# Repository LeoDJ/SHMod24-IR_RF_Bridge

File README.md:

# SHMod24 Addon: RF/IR Bridge

This addon is meant to be plugged onto a [SHMod24](https://github.com/LeoDJ/SHMod24) base board.
It provides the ability to send and receive infrared and 433MHz RF remote control codes.

**Current status**: a prototype PCB batch has been ordered and will be tested for functionality

## 3D Preview

|  |  |
| :--------------- | :------------------ |
|              |                 |

## BOM
There are multiple different module groups that can be populated.

 In the table is listed, which components to populate for a given module:

| Module                         | Reference | Part                    |
| :----------------------------- | :-------- | :---------------------- |
| **IR LED Array**               | Q1        | AO3400A                 |
|                                | R1        | 15Ω                     |
|                                | R2        | 10k                     |
|                                | R3, R4    | 2Ω                      |
|                                | C1        | 22µF, 1210              |
|                                | D1 - D7   | IR LED 5mm              |
|                                |           |                         |
| **IR Receiver Array**          | R7        | 100Ω                    |
|                                | C4        | 100µF, 6.3x5.8          |
|                                | R8        | 47k                     |
|                                | C6 - C9   | 100n                    |
|                                | IR1 - IR4 | VS1838b                 |
|                                |           |                         |
| **433MHz 12V Boost Converter** | U1        | MT3608                  |
| Can also be bypassed by        | R5        | 180k                    |
| bridging L1 and D8 to run      | R6        | 10k                     |
| 433MHz transmitter at 3.3V     | D8        | SS34 Schottky, SMA      |
|                                | C2, C3    | 22µF, 1210              |
|                                | L1        | 4.7µH, 0630             |
|                                |           |                         |
| **433MHz Receiver**            | RF1       | Generic China 433MHz RX |
|                                |           |                         |
| **433MHz Transmitter**         | RF2       | Generic China 433MHz TX |

## Project installation
- Make sure to run `git clone` with `--recurse-submodules` to include the necessary libraries too.

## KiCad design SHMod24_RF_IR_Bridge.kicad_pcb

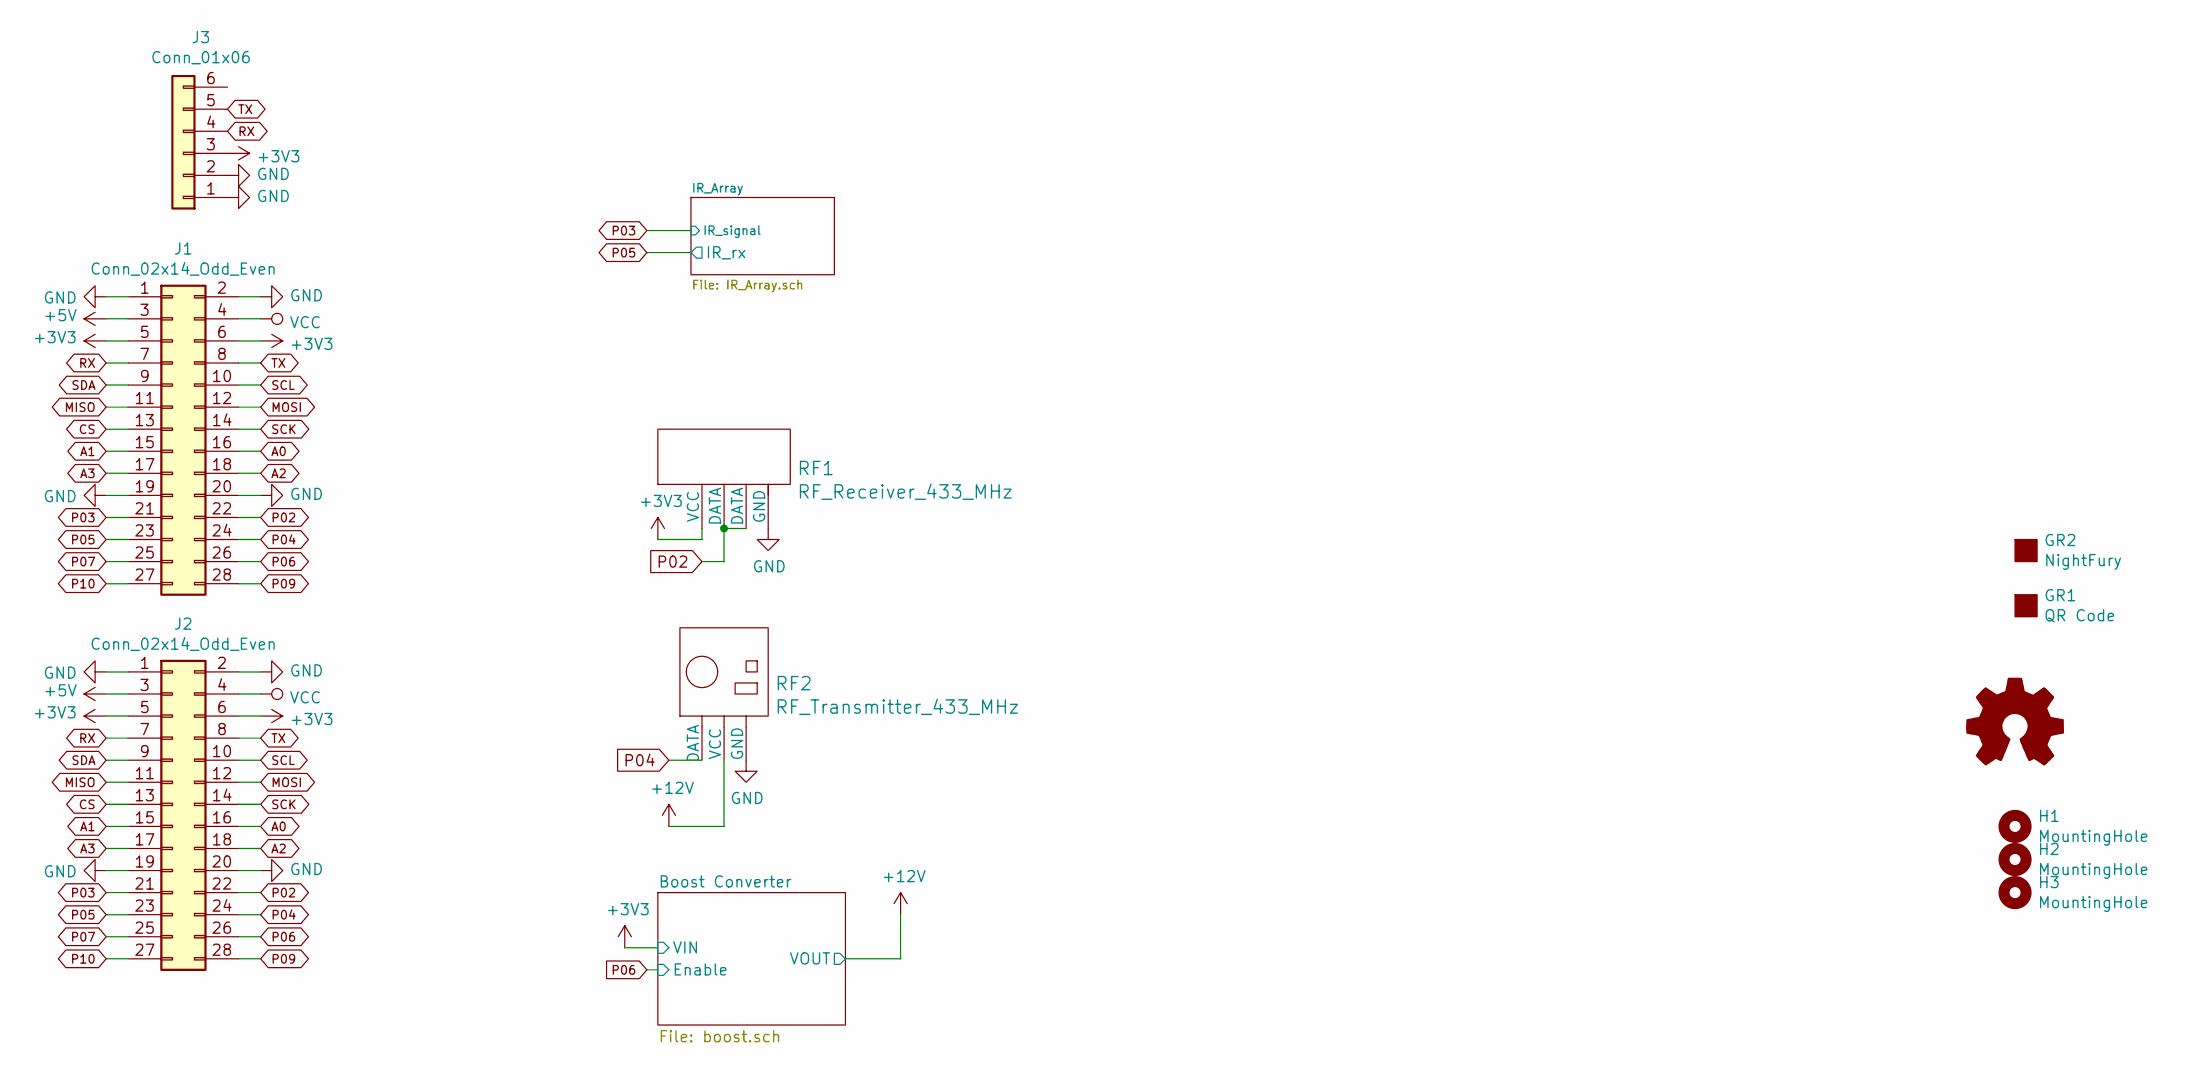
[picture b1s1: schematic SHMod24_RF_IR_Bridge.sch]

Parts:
GR1: QR Code; QR_Code_SHMod24-IRRF
GR2: NightFury; NightFury_Roll_8.0x6.1
H1, H2, H3: MountingHole; MountingHole_3.2mm_M3
J1: Conn_02x14_Odd_Even; PinSocket_2x14_P2.54mm_Vertical
J2: Conn_02x14_Odd_Even; PinSocket_2x14_P2.54mm_Vertical_SMD
J3: Conn_01x06; PinHeader_1x06_P2.54mm_Vertical
LOGO1: Logo_Open_Hardware_Small; OSHW-Logo2_7.3x6mm_SilkScreen
RF1: RF_Receiver_433_MHz
RF2: RF_Transmitter_433_MHz

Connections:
+3V3: J1.5, J1.6, J2.5, J2.6, J3.3, RF1.1 (VCC); also elsewhere on the board
+5V: J1.3, J2.3
+12V: RF2.2 (VCC); also elsewhere on the board
A0: J1.16, J2.16
A1: J1.15, J2.15
A2: J1.18, J2.18
A3: J1.17, J2.17
CS: J1.13, J2.13
GND: J1.1, J1.2, J1.19, J1.20, J2.1, J2.2, J2.19, J2.20, J3.1, J3.2, RF1.4 (GND), RF2.3 (GND); also elsewhere on the board
MISO: J1.11, J2.11
MOSI: J1.12, J2.12
P02: J1.22, J2.22, RF1.2 (DATA), RF1.3 (DATA)
P03: J1.21, J2.21; also elsewhere on the board
P04: J1.24, J2.24, RF2.1 (DATA)
P05: J1.23, J2.23; also elsewhere on the board
P06: J1.26, J2.26; also elsewhere on the board
P07: J1.25, J2.25
P09: J1.28, J2.28
P10: J1.27, J2.27
RX: J1.7, J2.7, J3.4
SCK: J1.14, J2.14
SCL: J1.10, J2.10
SDA: J1.9, J2.9
TX: J1.8, J2.8, J3.5
VCC: J1.4, J2.4

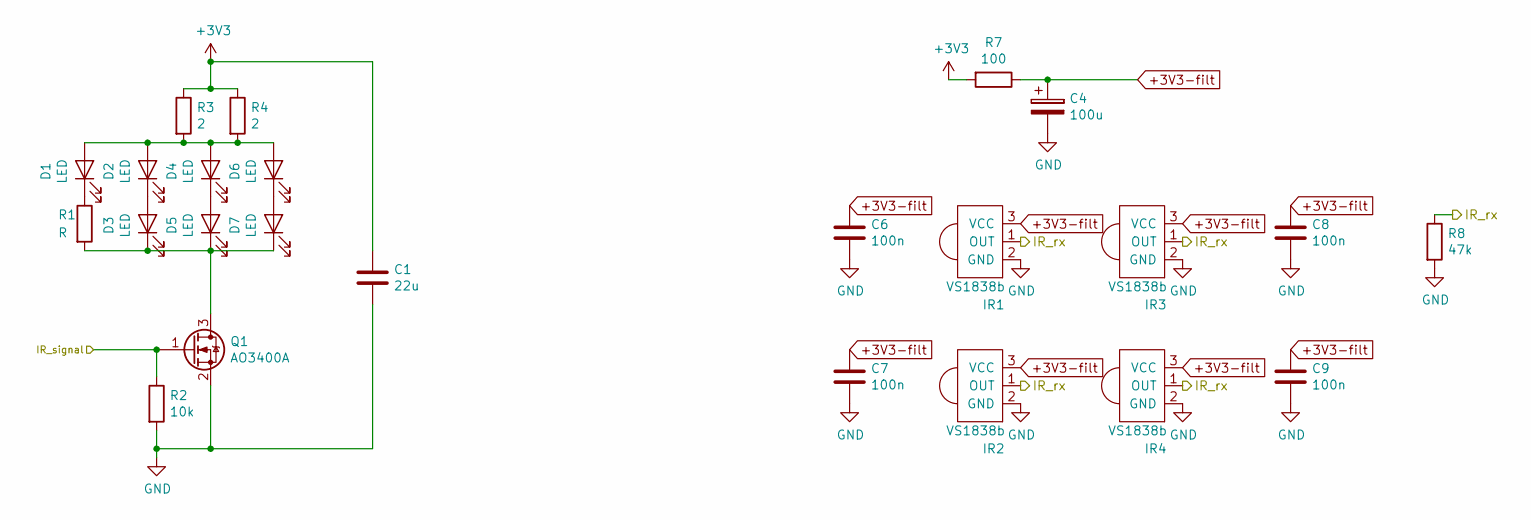
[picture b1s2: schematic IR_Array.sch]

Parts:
C1: 22u; C_1210_3225Metric
C4: 100u; CP_Elec_6.3x5.8
C6, C7, C8, C9: 100n; C_0805_2012Metric
D1: LED; LED_D5.0mm_IRBlack
D2, D3, D4, D5, D6, D7: LED; LED_D5.0mm_Horizontal_O1.27mm_Z9.0mm
IR1, IR2, IR3, IR4: VS1838b
Q1: AO3400A; SOT-23
R1: R; R_0805_2012Metric
R2: 10k; R_0805_2012Metric
R3, R4: 2; R_0805_2012Metric
R7: 100; R_0805_2012Metric
R8: 47k; R_0805_2012Metric

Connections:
+3V3: C1.1, R3.1, R4.1, R7.2; also elsewhere on the board
+3V3-filt: C4.1, C6.1, C7.1, C8.1, C9.1, IR1.3 (VCC), IR2.3 (VCC), IR3.3 (VCC), IR4.3 (VCC), R7.1
GND: C1.2, C4.2, C6.2, C7.2, C8.2, C9.2, IR1.2 (GND), IR2.2 (GND), IR3.2 (GND), IR4.2 (GND), Q1.2 (S), R2.2, R8.2; also elsewhere on the board
unnamed: D1.1 (K), R1.1
unnamed: D1.2 (A), D2.2 (A), D4.2 (A), D6.2 (A), R3.2, R4.2
unnamed: D2.1 (K), D3.2 (A)
unnamed: D3.1 (K), D5.1 (K), D7.1 (K), Q1.3 (D), R1.2
unnamed: D4.1 (K), D5.2 (A)
unnamed: D6.1 (K), D7.2 (A)
P03: Q1.1 (G), R2.1; also elsewhere on the board
P05: IR1.1 (OUT), IR2.1 (OUT), IR3.1 (OUT), IR4.1 (OUT), R8.1; also elsewhere on the board

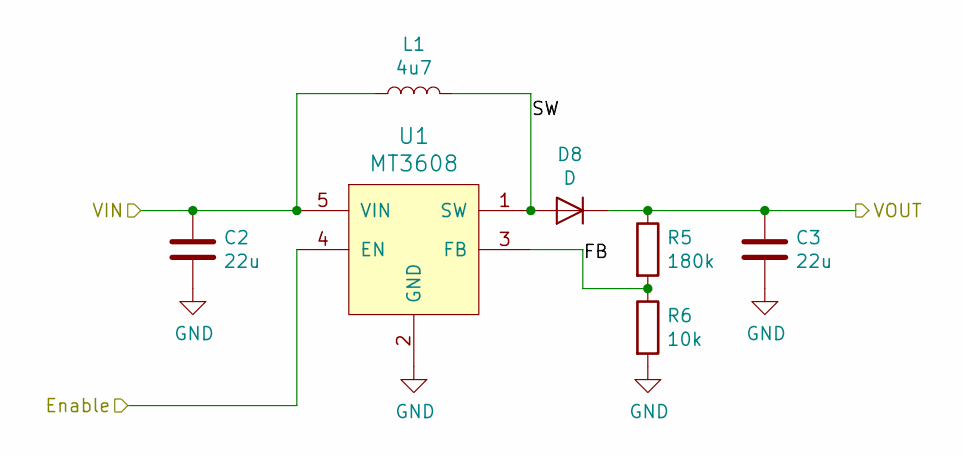
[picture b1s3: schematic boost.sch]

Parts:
C2, C3: 22u; C_1210_3225Metric
D8: D; D_SMA
L1: 4u7; L_0630
R5: 180k; R_0805_2012Metric
R6: 10k; R_0805_2012Metric
U1: MT3608; SOT-23-6

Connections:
+3V3: C2.1, L1.1, U1.5 (VIN); also elsewhere on the board
+12V: C3.1, D8.1 (K), R5.1; also elsewhere on the board
/Boost Converter/FB: R5.2, R6.1, U1.3 (FB)
/Boost Converter/SW: D8.2 (A), L1.2, U1.1 (SW)
GND: C2.2, C3.2, R6.2, U1.2 (GND); also elsewhere on the board
P06: U1.4 (EN); also elsewhere on the board

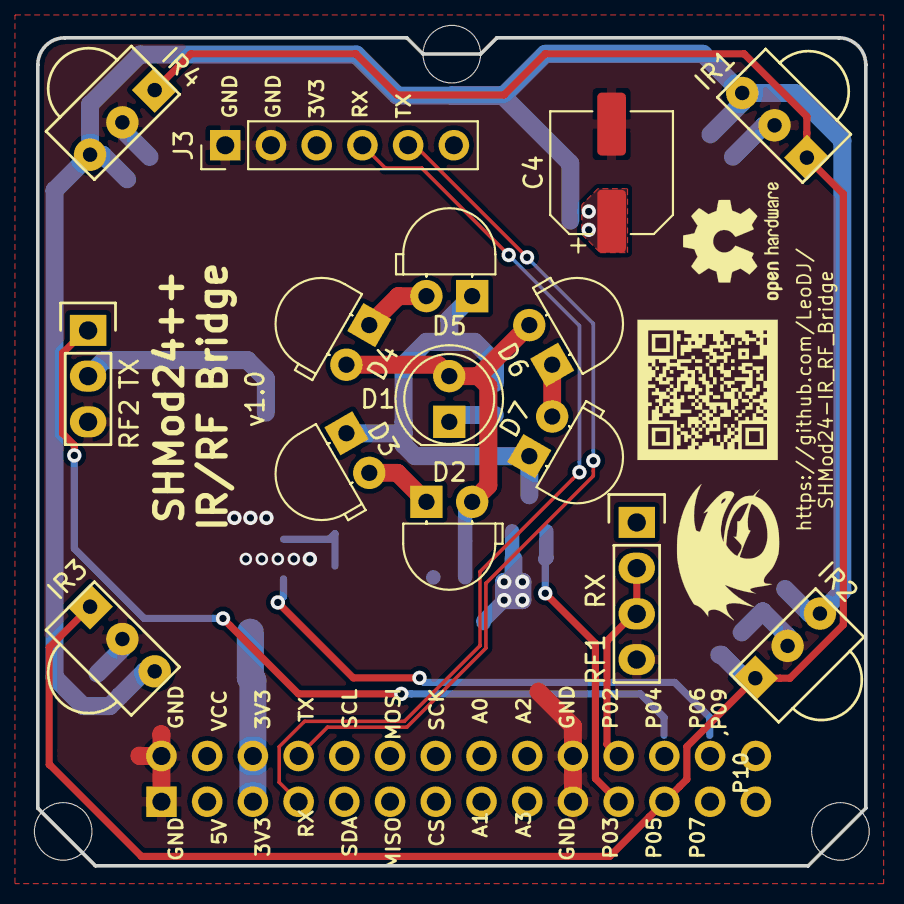
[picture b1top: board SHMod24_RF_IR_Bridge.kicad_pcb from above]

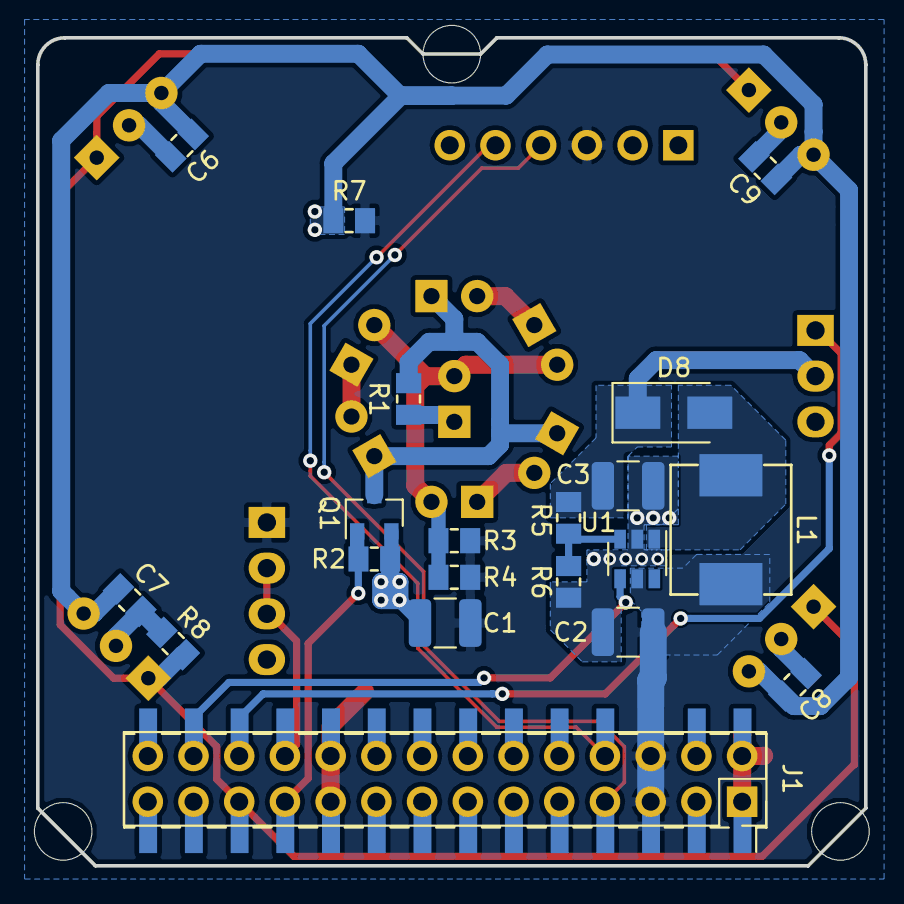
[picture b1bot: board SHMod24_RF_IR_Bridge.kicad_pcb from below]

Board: 2 copper layers, 46.0 x 46.0 mm, 42 parts (21 on the bottom side), 34 nets.

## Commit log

2019-01-15 initial commit
    basic SHMod24 addon board layout with holes and header done
2019-01-16 add smd pin header option
2019-01-17 design IR send / receive
2019-01-30 add boost converter, IR RX, 433MHz RX/TX and labels
2019-01-30 add serial comms header
2019-02-04 final touches
2019-02-04 generate gerbers
2019-04-23 add BOM
2021-03-10 Create LICENSE
